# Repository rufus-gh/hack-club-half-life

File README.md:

# 3-Bit Binary Adder Circuit

I am making a PCB where you can enter 2 3-bit binary numbers using slide switches, and then it outputs them added via LEDs.

I first designed the logic circuit in Sebastian Lague's Digital Logic Sim, and then converted it to a schematic in Kicad and then a PCB which I used Freerouting to auto-route it. 

# BOM

| Week | Tier | Parts funding |
| --- | --- | --- |
| Week 1 | Tier 1 | $30.00 |

| Part | What it's for | Qty | Unit | Total | Vendor |
| --- | --- | --- | --- | --- | --- |
| [PCB from JLCPCB](https://jlcpcb.com) | The pcb | 1 | $4.00 | $4.00 | [JLCPCB](https://jlcpcb.com) |
| [10x 74hc00](https://www.aliexpress.com/item/1005008583582387.html?spm=a2g0o.cart.0.0.202b38daBqYS5y&mp=1&pdp_npi=6@dis!AUD!AUD%201.12!AUD%201.12!!AUD%201.12!!!@2101c4b817917647332913856e0e42!12000045830763407!ct!AU!8282893199!!1!0!) | NAND gates | 1 | $1.12 | $1.12 | [Aliexpress](https://www.aliexpress.com/item/1005008583582387.html?spm=a2g0o.cart.0.0.202b38daBqYS5y&mp=1&pdp_npi=6@dis!AUD!AUD%201.12!AUD%201.12!!AUD%201.12!!!@2101c4b817917647332913856e0e42!12000045830763407!ct!AU!8282893199!!1!0!) |
| [LEDs and resistors](https://www.aliexpress.com/item/1005007592187428.html?spm=a2g0o.cart.0.0.202b38daBqYS5y&mp=1&pdp_npi=6@dis!AUD!AUD%2013.36!AUD%206.88!!AUD%206.88!!!@2101c4b817917647332913856e0e42!12000041421584236!ct!AU!8282893199!!1!0!) | Glowing | 1 | $6.88 | $6.88 | [Aliexpress](https://www.aliexpress.com/item/1005007592187428.html?spm=a2g0o.cart.0.0.202b38daBqYS5y&mp=1&pdp_npi=6@dis!AUD!AUD%2013.36!AUD%206.88!!AUD%206.88!!!@2101c4b817917647332913856e0e42!12000041421584236!ct!AU!8282893199!!1!0!) |
| [10x 14 pin IC sockets](https://www.aliexpress.com/item/1005007539941715.html?spm=a2g0o.cart.0.0.202b38daBqYS5y&mp=1&pdp_npi=6@dis!AUD!AUD%206.12!AUD%202.94!!AUD%202.94!!!@2101c4b817917647332913856e0e42!12000041213583452!ct!AU!8282893199!!2!0!) | To solder to PCB without damaging IC | 2 | $2.94 | $5.88 | [Aliexpress](https://www.aliexpress.com/item/1005007539941715.html?spm=a2g0o.cart.0.0.202b38daBqYS5y&mp=1&pdp_npi=6@dis!AUD!AUD%206.12!AUD%202.94!!AUD%202.94!!!@2101c4b817917647332913856e0e42!12000041213583452!ct!AU!8282893199!!2!0!) |
| [10x 74hc00](https://www.aliexpress.com/item/1005006186781850.html?spm=a2g0o.cart.0.0.202b38daBqYS5y&mp=1&pdp_npi=6@dis!AUD!AUD%208.11!AUD%202.69!!AUD%202.69!!!@2101c4b817917647332913856e0e42!12000036217497113!ct!AU!8282893199!!1!0!) | NAND gates | 1 | $1.49 | $1.49 | [Aliexpress](https://www.aliexpress.com/item/1005006186781850.html?spm=a2g0o.cart.0.0.202b38daBqYS5y&mp=1&pdp_npi=6@dis!AUD!AUD%208.11!AUD%202.69!!AUD%202.69!!!@2101c4b817917647332913856e0e42!12000036217497113!ct!AU!8282893199!!1!0!) |
| [20x micro slide switches](https://www.aliexpress.com/item/1005003938407295.html?spm=a2g0o.cart.0.0.202b38daBqYS5y&mp=1&pdp_npi=6@dis!AUD!AUD%203.62!AUD%203.62!!AUD%203.62!!!@2101c4b817917647332913856e0e42!12000053184498269!ct!AU!8282893199!!1!0!&pdp_ext_f=%7B%22cart2PdpParams%22:%7B%22pdpBusinessMode%22:%22retail%22%7D%7D) | Representing the binary numbers | 1 | $1.49 | $1.49 | [Aliexpress](https://www.aliexpress.com/item/1005003938407295.html?spm=a2g0o.cart.0.0.202b38daBqYS5y&mp=1&pdp_npi=6@dis!AUD!AUD%203.62!AUD%203.62!!AUD%203.62!!!@2101c4b817917647332913856e0e42!12000053184498269!ct!AU!8282893199!!1!0!&pdp_ext_f=%7B%22cart2PdpParams%22:%7B%22pdpBusinessMode%22:%22retail%22%7D%7D) |
| **Parts subtotal** | — | — | — | **$20.86** | — |
| **Tax & shipping** | — | — | — | **$9.14** | — |
| **Total** | — | — | — | **$30.00** | — |

$0.00 left of the tier's funding.

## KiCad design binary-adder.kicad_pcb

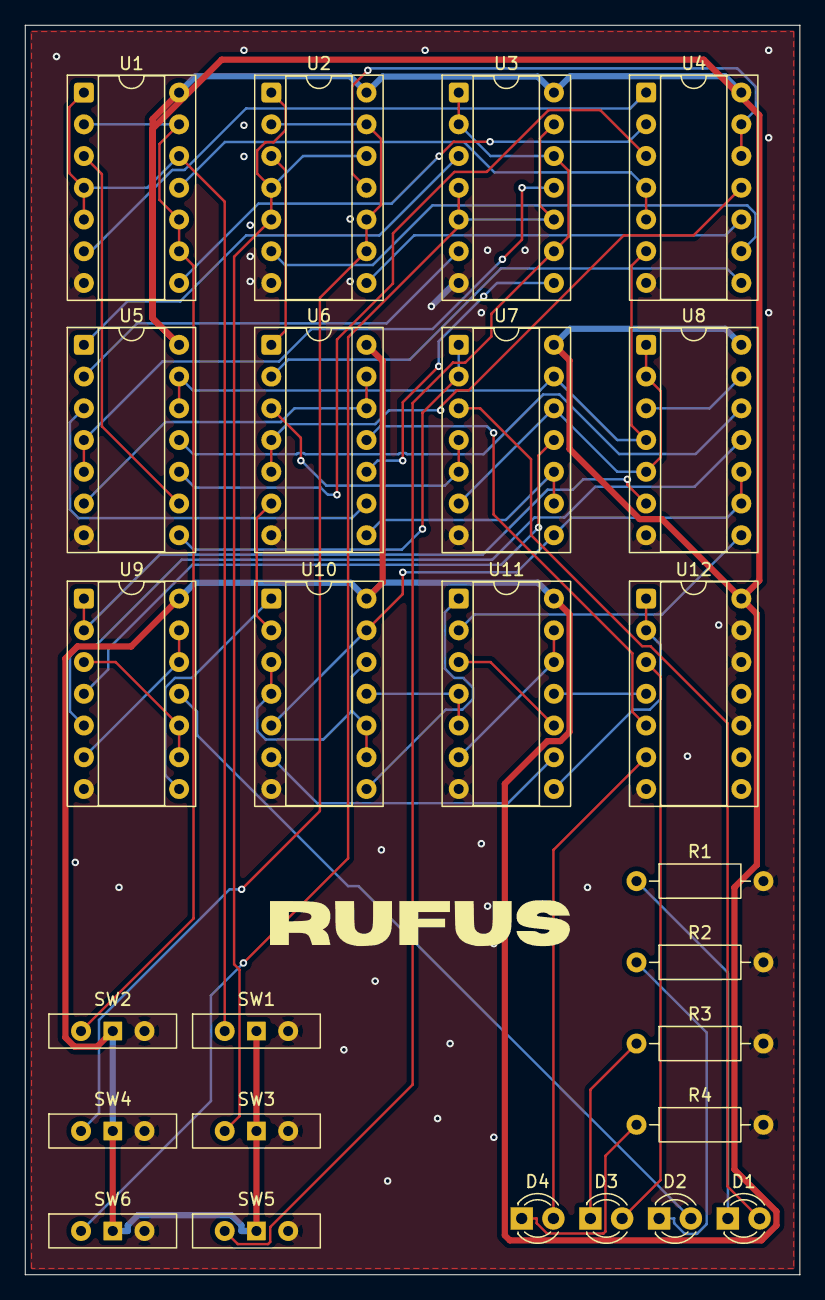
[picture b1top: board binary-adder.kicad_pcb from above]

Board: 2 copper layers, 62.0 x 100.0 mm, 27 parts (0 on the bottom side), 58 nets.

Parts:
 : LOGO; rufus-logo
D1, D2, D3, D4: LED; LED_D3.0mm
R1, R2, R3, R4: 330; R_Axial_DIN0207_L6.3mm_D2.5mm_P10.16mm_Horizontal
SW1, SW2, SW3, SW4, SW5, SW6: SW_SPDT; SW_Slide-03_Wuerth-WS-SLTV_10x2.5x6.4_P2.54mm
U1, U2, U3, U4, U5, U6, U7, U8, U9, U10, U11, U12: 74HC00; DIP-14_W7.62mm_Socket

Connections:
+5V: SW1.1 (A), SW2.1 (A), SW3.1 (A), SW4.1 (A), SW5.1 (A), SW6.1 (A), U1.14 (VCC), U2.14 (VCC), U3.14 (VCC), U4.14 (VCC), U5.14 (VCC), U6.14 (VCC), U7.14 (VCC), U8.14 (VCC), U9.14 (VCC), U10.14 (VCC), U11.14 (VCC), U12.14 (VCC)
GND: R1.2, R2.2, R3.2, R4.2, SW1.3 (C), SW2.3 (C), SW3.3 (C), SW4.3 (C), SW5.3 (C), SW6.3 (C), U1.7 (GND), U2.7 (GND), U3.7 (GND), U4.7 (GND), U5.7 (GND), U6.7 (GND), U7.7 (GND), U8.7 (GND), U9.7 (GND), U10.7 (GND), U11.7 (GND), U12.7 (GND), U12.9, U12.10, U12.12, U12.13
unnamed: D1.2 (A), U7.3
unnamed: D1.1 (K), R1.1
unnamed: D2.2 (A), U9.11
unnamed: D2.1 (K), R2.1
unnamed: D3.2 (A), U12.3
unnamed: D3.1 (K), R3.1
unnamed: D4.2 (A), U12.6
unnamed: D4.1 (K), R4.1
unnamed: SW1.2 (B), U1.1, U1.4, U1.5, U1.12
unnamed: SW2.2 (B), U1.2, U1.9, U1.10, U1.13
unnamed: SW3.2 (B), U2.1, U2.4, U2.5, U2.12
unnamed: SW4.2 (B), U2.2, U2.9, U2.10, U2.13
unnamed: SW5.2 (B), U3.1, U3.2, U3.9, U3.12
unnamed: SW6.2 (B), U3.4, U3.5, U3.10, U3.13
unnamed: U1.3, U5.9
unnamed: U1.6, U4.1
unnamed: U1.8, U4.2
unnamed: U1.11, U4.4, U4.5
unnamed: U2.3, U6.1
unnamed: U2.6, U4.9
unnamed: U2.8, U4.10
unnamed: U2.11, U4.12, U4.13
unnamed: U3.3, U5.1
unnamed: U3.6, U5.2
unnamed: U3.8, U6.10
unnamed: U3.11, U5.4, U5.5
unnamed: U4.3, U5.10
unnamed: U4.6, U5.12, U5.13, U7.13, U8.4
unnamed: U4.8, U6.2
unnamed: U4.11, U6.4, U6.5
unnamed: U5.3, U6.9
unnamed: U5.6, U6.12, U6.13
unnamed: U5.8, U7.1, U7.2
unnamed: U5.11, U8.12
unnamed: U6.3, U7.4, U7.5
unnamed: U6.8, U7.9, U7.10
unnamed: U7.11, U9.4
unnamed: U7.6, U7.12, U8.1, U8.2, U8.5
unnamed: U8.6, U9.1, U9.2
unnamed: U8.11, U9.5
unnamed: U8.3, U8.13
unnamed: U9.3, U9.9, U9.10
unnamed: U9.6, U9.12, U9.13
unnamed: U9.8, U10.1
unnamed: U6.6, U10.2
unnamed: U10.6, U11.9
unnamed: U10.8, U11.1
unnamed: U10.3, U10.4, U10.9, U10.10, U10.12
unnamed: U10.11, U11.4, U11.5
unnamed: U7.8, U8.9, U8.10, U10.5, U10.13
unnamed: U8.8, U11.2
unnamed: U11.8, U12.1, U12.2
unnamed: U11.3, U11.10
unnamed: U11.11, U12.4
unnamed: U11.6, U11.12, U11.13
unnamed: U6.11, U12.5
